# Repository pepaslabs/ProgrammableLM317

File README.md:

# ProgrammableLM317

A TTL-serial programmable LM317 voltage voltage supply circuit board design.

Schematic: [pdf](kicad/releases/v2.1/ProgrammableLM317.pdf).

Gerbers: [zip](kicad/releases/v2.1/gerbers.zip)

OSHPark: [link](https://oshpark.com/shared_projects/kM7WPtAO)

## License

This board design is [Open-Source Hardware](http://www.oshwa.org/definition/).  It is licensed under the [MIT License](http://opensource.org/licenses/MIT).  It was designed by Jason Pepas.

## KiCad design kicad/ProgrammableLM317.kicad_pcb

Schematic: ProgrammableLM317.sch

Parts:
C1: 10uF
C2, C3, C4, C6, C7, C8, C9: 0.1uF
C10: 10nF
D1, D2: 1N4001
H1, H2, H3, H4: HOLE
IC1: ATTINY85-P; DIP8
P1, P2: CONN_2
P3: CONN_4
R1: 33k
R2: 10k
R3: 1.5k
U1: LM317
U2: LM358
U3: MCP4801; DIP8
U4: 7805

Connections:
5V: C4.1, C6.1, C7.1, IC1.8 (VCC), P3.1, U2.5 (+), U3.1 (VDD), U3.6 (~SHDN~), U4.3 (OUT)
GND: C1.2, C2.2, C3.2, C4.2, C6.2, C7.2, C8.2, C9.2, C10.2, IC1.4 (GND), P1.2 (PM), P2.2 (PM), P3.4, R2.2, R3.2, U2.4 (V-), U3.5 (~LDAC~), U3.7 (VSS), U4.2 (GND)
unnamed: IC1.5 (PB0(MOSI/DI/SDA/AIN0/OC0A/OC1A/AREF/PCI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), U3.4 (SDI)
unnamed: IC1.6 (PB1(MISO/DO/AIN1/OC0B/OC1A/PCINT1)), U3.3 (SCK)
unnamed: IC1.7 (PB2(SCK/USCK/SCL/T0/INT0/ADC1/PCINT2)), U3.2 (~CS~)
unnamed: U2.6 (-), U2.7
unnamed: D2.1 (A), R1.1, U1.1 (ADJ), U2.1
unnamed: C10.1, R1.2, R2.1, U2.2 (-)
unnamed: U2.3 (+), U3.8 (Vout)
RX: IC1.2 (PB3(XTAL1/CLKI/OC1B/ADC3/PCINT3)), P3.2
TX: IC1.3 (PB4(XTAL2/CLKO/OC1B/ADC2/PCINT4)), P3.3
Vcc: C1.1, C3.1, C8.1, D1.2 (K), P1.1, U1.3 (IN), U2.8 (V+), U4.1 (IN)
Vout: C2.1, C9.1, D1.1 (A), D2.2 (K), P2.1, R3.1, U1.2 (OUT)

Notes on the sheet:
Gain = 4.3
0V to 4.096V in 16mV steps
8-bit DAC in 4.096V mode 1 LSB = 16mV
0V to 17.613V in 69mV steps
1.25V to 18.863V in 69mV steps
RS-232 (TTL)
Terminating the unused op amp

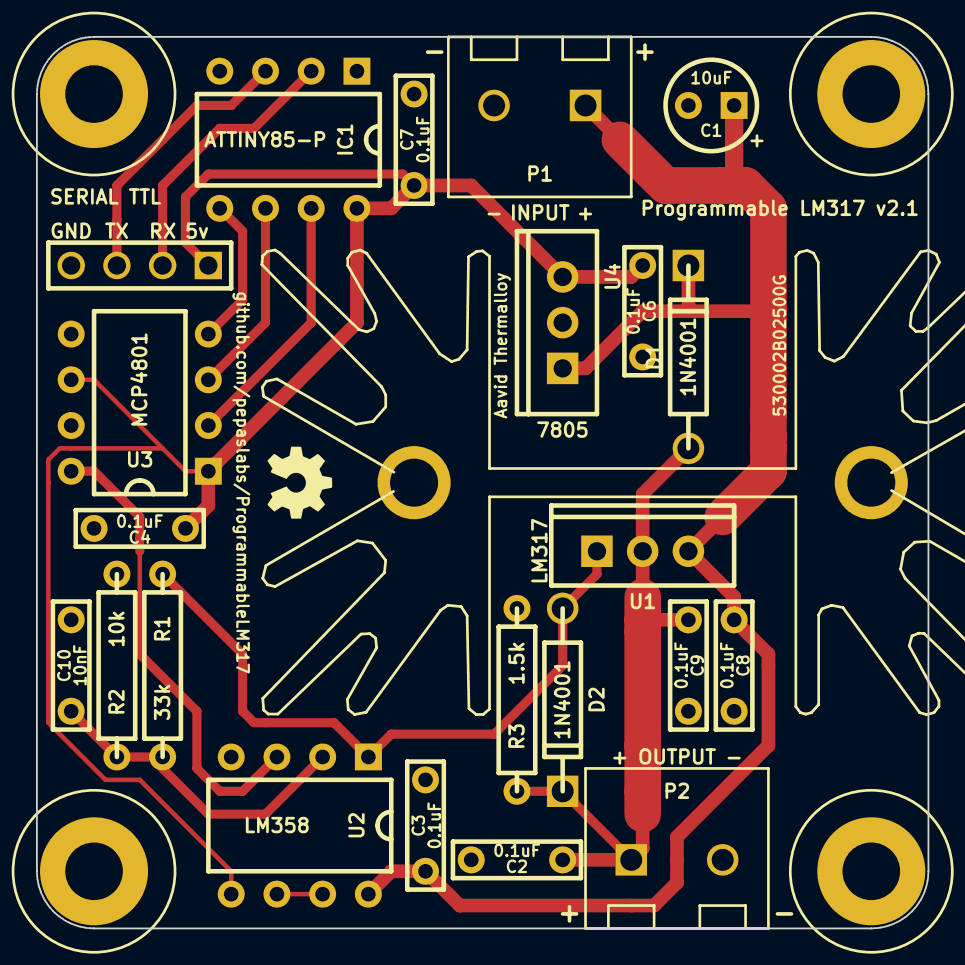
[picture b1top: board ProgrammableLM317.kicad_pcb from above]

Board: 2 copper layers, 49.5 x 49.5 mm, 27 parts (0 on the bottom side), 13 nets.

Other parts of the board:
H***: 530002B02500G

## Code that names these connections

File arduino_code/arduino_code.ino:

/*
  ATtiny85SerialHello.ino: Repeatedly print "hello" and blink an LED.
  Copyright Jason Pepas (Pepas Labs, LLC)
  Released under the terms of the MIT License.  See http://opensource.org/licenses/MIT
*/

#define __STDC_LIMIT_MACROS
#include <stdint.h>

#include <SoftwareSerial.h>
#include <WOTinySoftSPI.h>
#include <MCP4801SoftSPI.h>

#include "command_t.h"

// --- Feature toggles

#define HAS_INCREMENT_COMMAND
#define HAS_DECREMENT_COMMAND
#define HAS_VOLTS_COMMAND
#define HAS_HEX_COMMAND
//#define HAS_ERROR_PRINTING
//#define HAS_SUCCESS_PRINTING


// ATiny85 pinout:
//
//                                      +--\/--+
//        (PCINT5/!RESET/ADC0/dW) PB5  -|1    8|-  VCC
// (PCINT3/XTAL1/CLKI/!OC1B/ADC3) PB3  -|2    7|-  PB2 (SCK/USCK/SCL/ADC1/T0/INT0/PCINT2)
//  (PCINT4/XTAL2/CLKO/OC1B/ADC2) PB4  -|3    6|-  PB1 (MISO/DO/AIN1/OC0B/OC1A/PCINT1)
//                                GND  -|4    5|-  PB0 (MOSI/DI/SDA/AIN0/OC0A/!OC1A/AREF/PCINT0)
//                                      +------+

#define ARDUINO_PIN_D0 0
#define ARDUINO_PIN_D1 1
#define ARDUINO_PIN_D2 2
#define ARDUINO_PIN_D3 3
#define ARDUINO_PIN_D4 4
#define ARDUINO_PIN_D5 5

#define ATTINY_PIN_1 ARDUINO_PIN_D5
#define ATTINY_PIN_2 ARDUINO_PIN_D3
#define ATTINY_PIN_3 ARDUINO_PIN_D4
#define ATTINY_PIN_5 ARDUINO_PIN_D0
#define ATTINY_PIN_6 ARDUINO_PIN_D1
#define ATTINY_PIN_7 ARDUINO_PIN_D2

// project pinout:
//
//                      +--\/--+
//                 D5  -|1    8|-  Vcc
//  TTL serial RX  D3  -|2    7|-  D2  SPI chip select (to DAC)
//  TTL serial TX  D4  -|3    6|-  D1  SPI SCK (to DAC)
//                GND  -|4    5|-  D0  SPI MOSI (to DAC)
//                      +------+

#define SoftSPI_MOSI_pin ARDUINO_PIN_D0
#define SoftSPI_SCK_pin ARDUINO_PIN_D1
#define MCP4801_SLAVESELECTLOW_pin ARDUINO_PIN_D2
#define MCP4801_LDACLOW_pin PIN_NOT_CONNECTED
#define MCP4801_SHUTDOWNLOW_pin PIN_NOT_CONNECTED

#define RX_pin ARDUINO_PIN_D3
#define TX_pin ARDUINO_PIN_D4

// --- SPI / MCP4801 DAC setup

WOTinySoftSPI mySPI(SoftSPI_MOSI_pin, SoftSPI_SCK_pin);

MCP4801SoftSPI voltageDAC(MCP4801_SLAVESELECTLOW_pin,
                          MCP4801_LDACLOW_pin,
                          MCP4801_SHUTDOWNLOW_pin,
                          &mySPI
                         );

#define MCP4801_NUM_BITS 8
#define MCP4811_NUM_BITS 10
#define MCP4821_NUM_BITS 12

uint8_t DAC_num_bits = MCP4801_NUM_BITS;
uint16_t DAC_data = 0;

// --- serial port setup

SoftwareSerial serial(RX_pin, TX_pin);

/*

Serial terminal interface:

Set the output voltage to 5 volts:

    v5.000;

Set the bits in the DAC to 0xFF (8-bit DAC):

    xFF;

Set the bits in the DAC to 0x3FF (10-bit DAC):

    x3FF;

Set the bits in the DAC to 0xFFF (12-bit DAC):

    xFFF;

Increase the DAC output by one LSB:

    +;

Decrease the DAC output by one LSB:

    -;

*/

#define MIN_EXPECTED_LEN 2 // +;
#define MAX_EXPECTED_LEN 8 // v12.345;

#define BUFF_LEN (MAX_EXPECTED_LEN + sizeof('\0'))
char buffer[BUFF_LEN];
char *buff_ptr;

void setup()
{
  delay(1);
  serial.begin(9600);
  serial.print("OK;");
  serial.flush();
  
  // start up the SPI bus
  mySPI.begin();
  mySPI.setBitOrder(MSBFIRST);
  mySPI.setDataMode(SPI_MODE0);

  // start controlling the voltage supply
  voltageDAC.begin();  

  memset(buffer, 0, sizeof(buffer));
  buff_ptr = buffer;
}

void loop()
{
  command_t command = read_command(&serial, buffer, BUFF_LEN);
  if (command >= END_OF_COMMANDS_SECTION)
  {
    printError(command);
    return;
  }

  error_t error;
  
  if (command == COMMAND_INCREMENT)
  {
    error = increment_output_voltage();
  }
  else if (command == COMMAND_DECREMENT)
  {
    error = decrement_output_voltage();
  }
  else if (command == COMMAND_SET_VOLTS)
  {
    error = parse_and_run_voltage_command(buffer);
  }
  else if (command == COMMAND_SET_HEX)
  {
    error = parse_and_run_hex_command(buffer);
  }
  else
  {
    error = ERROR_UNKNOWN_COMMAND;
  }

  if (error != OK_NO_ERROR)
  {
    printError(error);
    return;
  }
  
  printSuccess(command);
}

command_t read_command(SoftwareSerial *serial, char *buffer, uint8_t buff_len)
{
  // --- read the first character
  
  while(serial->available() == 0)
  {
    continue;
  }
    
  char ch = serial->read();
  
  if (ch == '+')
  {
    uint8_t num_chars_consumed = consume_until_sentinel(serial, ';');
    if (num_chars_consumed == 1)
    {
      return COMMAND_INCREMENT;
    }
    else
    {
      return ERROR_PARSING_INCREMENT_COMMAND;
    }
  }
  else if (ch == '-')
  {
    uint8_t num_chars_consumed = consume_until_sentinel(serial, ';');
    if (num_chars_consumed == 1)
    {
      return COMMAND_DECREMENT;
    }
    else
    {
      return ERROR_PARSING_DECREMENT_COMMAND;
    }
  }
  else if (ch == 'x')
  {
    // prepend buffer with '0x'
    buffer[0] = '0';
    buffer[1] = 'x';
    buff_ptr = buffer+2;
    
    // read the hex characters into buffer
    error_t error = read_until_sentinel(serial, buffer, buff_len-2, ';');    
    if (error == OK_NO_ERROR)
    {
      return COMMAND_SET_HEX;
    }
    else // i.e. if (error == ERROR_BUFFER_FILLED_UP_BEFORE_SENTINEL_REACHED)
    {      
      return ERROR_BUFFER_FILLED_UP_BEFORE_SENTINEL_REACHED_WHILE_PARSING_HEX_COMMAND;
    }
  }
  else if (ch == 'v')
  {
    // read the floating point string into buffer
    error_t error = read_until_sentinel(serial, buffer, buff_len, ';');
    if (error == OK_NO_ERROR)
    {
      return COMMAND_SET_VOLTS;
    }
    else // i.e. if (error == ERROR_BUFFER_FILLED_UP_BEFORE_SENTINEL_REACHED)
    {      
      return ERROR_BUFFER_FILLED_UP_BEFORE_SENTINEL_REACHED_WHILE_PARSING_VOLTS_COMMAND;
    }
  }
  else
  {
    return ERROR_UNKNOWN_COMMAND;
  }
}

uint8_t consume_until_sentinel(SoftwareSerial *serial, char sentinel)
{
  uint8_t num_chars_consumed = 0;
  
  while(true)
  {
    while(serial->available() == 0)
    {
      continue;
    }
    
    char ch = serial->read();
    num_chars_consumed++;
    
    if (ch == sentinel || num_chars_consumed == UINT8_MAX)
    {
      return num_chars_consumed;
    }
  }
}

error_t read_until_sentinel(SoftwareSerial *serial, char *buffer, uint8_t buff_len, char sentinel)
{
  uint8_t num_chars_consumed = 0;
  char *buff_ptr = buffer;
  
  while(true)
  {
    while(serial->available() == 0)
    {
      continue;
    }
    
    *buff_ptr = serial->read();
    num_chars_consumed++;

    if (*buff_ptr == sentinel)
    {
      *buff_ptr = '\0';
      return OK_NO_ERROR;
    }
    else if (num_chars_consumed == buff_len-1)
    {
      *buff_ptr = '\0';
      return ERROR_BUFFER_FILLED_UP_BEFORE_SENTINEL_REACHED;
    }
    else
    {
      buff_ptr++;
      continue;
    }  
  }
}

void printError(error_t error)
{
#ifdef HAS_ERROR_PRINTING
  serial.print("!e");
  serial.print(error);
  serial.print(";");
  serial.flush();
#endif
}

void printSuccess(command_t command)
{
#ifdef HAS_SUCCESS_PRINTING
  serial.print("ok");
  serial.print(command);
  serial.print(";");
  serial.flush();
#endif
}

bool DAC_would_overflow(uint8_t num_bits)
{
  return DAC_data == (1 << num_bits) - 1;
}

bool DAC_would_underflow()
{
  return DAC_data == 0;
}

void set_DAC_bits(uint8_t bits)
{
  bool use_2x_gain = true;
  voltageDAC.setVoltageOutputBits(bits, use_2x_gain);
}

#ifdef HAS_INCREMENT_COMMAND
error_t increment_output_voltage()
{
  if (DAC_would_overflow(DAC_num_bits))
  {
    return ERROR_INCREMENT_WOULD_CAUSE_OVERFLOW;
  }

  DAC_data++;
  set_DAC_bits(DAC_data);
  return OK_NO_ERROR;
}
#endif

#ifdef HAS_DECREMENT_COMMAND
error_t decrement_output_voltage()
{
  if (DAC_would_underflow())
  {
    return ERROR_DECREMENT_WOULD_CAUSE_UNDERFLOW;
  }

  DAC_data--;
  set_DAC_bits(DAC_data);
  return OK_NO_ERROR;
}
#endif

#ifdef HAS_VOLTS_COMMAND
error_t parse_and_run_voltage_command(char *buffer)
{
  float v = atof(buffer);
  
  // debug
  serial.println();
  serial.print("parsed volts: ");
  serial.println(v);
  serial.flush();
  
  DAC_data = voltageDAC.setVoltageOutput(v);
  return OK_NO_ERROR;
}
#endif

#ifdef HAS_HEX_COMMAND
error_t parse_and_run_hex_command(char *buffer)
{
  uint16_t bits = 0;
  int num_matches_found = sscanf(buffer, "%x", &bits);
  if (num_matches_found != 1)
  {
    return ERROR_PARSING_HEX_VALUE;
  }

  DAC_data = bits;
  set_DAC_bits(DAC_data);
  return OK_NO_ERROR;
}
#endif

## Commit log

2015-03-26 pulling in v1 board design.
2015-03-26 adding protection diodes to for the LM317.
2015-03-26 removing superfluous capacitors
2015-03-26 adding protection diodes to board layout
2015-03-26 staging the v2 release
2015-03-26 forgot to update the fill plane after moving some parts around.
2015-03-26 updating board renders
2015-03-28 adding initial attempt at writing an Arduino sketch for this.
2015-03-28 working rewriting the serial read loop
2015-03-29 reworked the error / command codes. working on feature toggles to allow smaller binaries (maybe ATtiny45?).
2015-03-29 got feature toggling implemented.
2015-03-31 renaming firmware sketch
2015-03-31 working on Arduino firmware sketch for the ATtiny85.
2015-04-07 rearranging schematic.
2015-04-07 adding parsing of dac "code. adding gain and offset to output volts command.
2015-04-07 working on adding op amp gain calibration and LM317 VREF offset calibration.
2015-04-07 working on gain and offset calibration support.
2015-04-08 working on EEPROM-backed digital calibration values
2015-04-08 removing HEX command
2015-04-08 formatting
2015-04-08 got all commands to fit in 8KB.
2015-04-08 code organization
2015-04-08 implementing dump command
2018-02-26 v2.1
2018-02-26 board shots
